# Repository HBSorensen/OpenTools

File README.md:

# OpenTools
Collection of  Tools (Both hardware and software) for various software and hardware development

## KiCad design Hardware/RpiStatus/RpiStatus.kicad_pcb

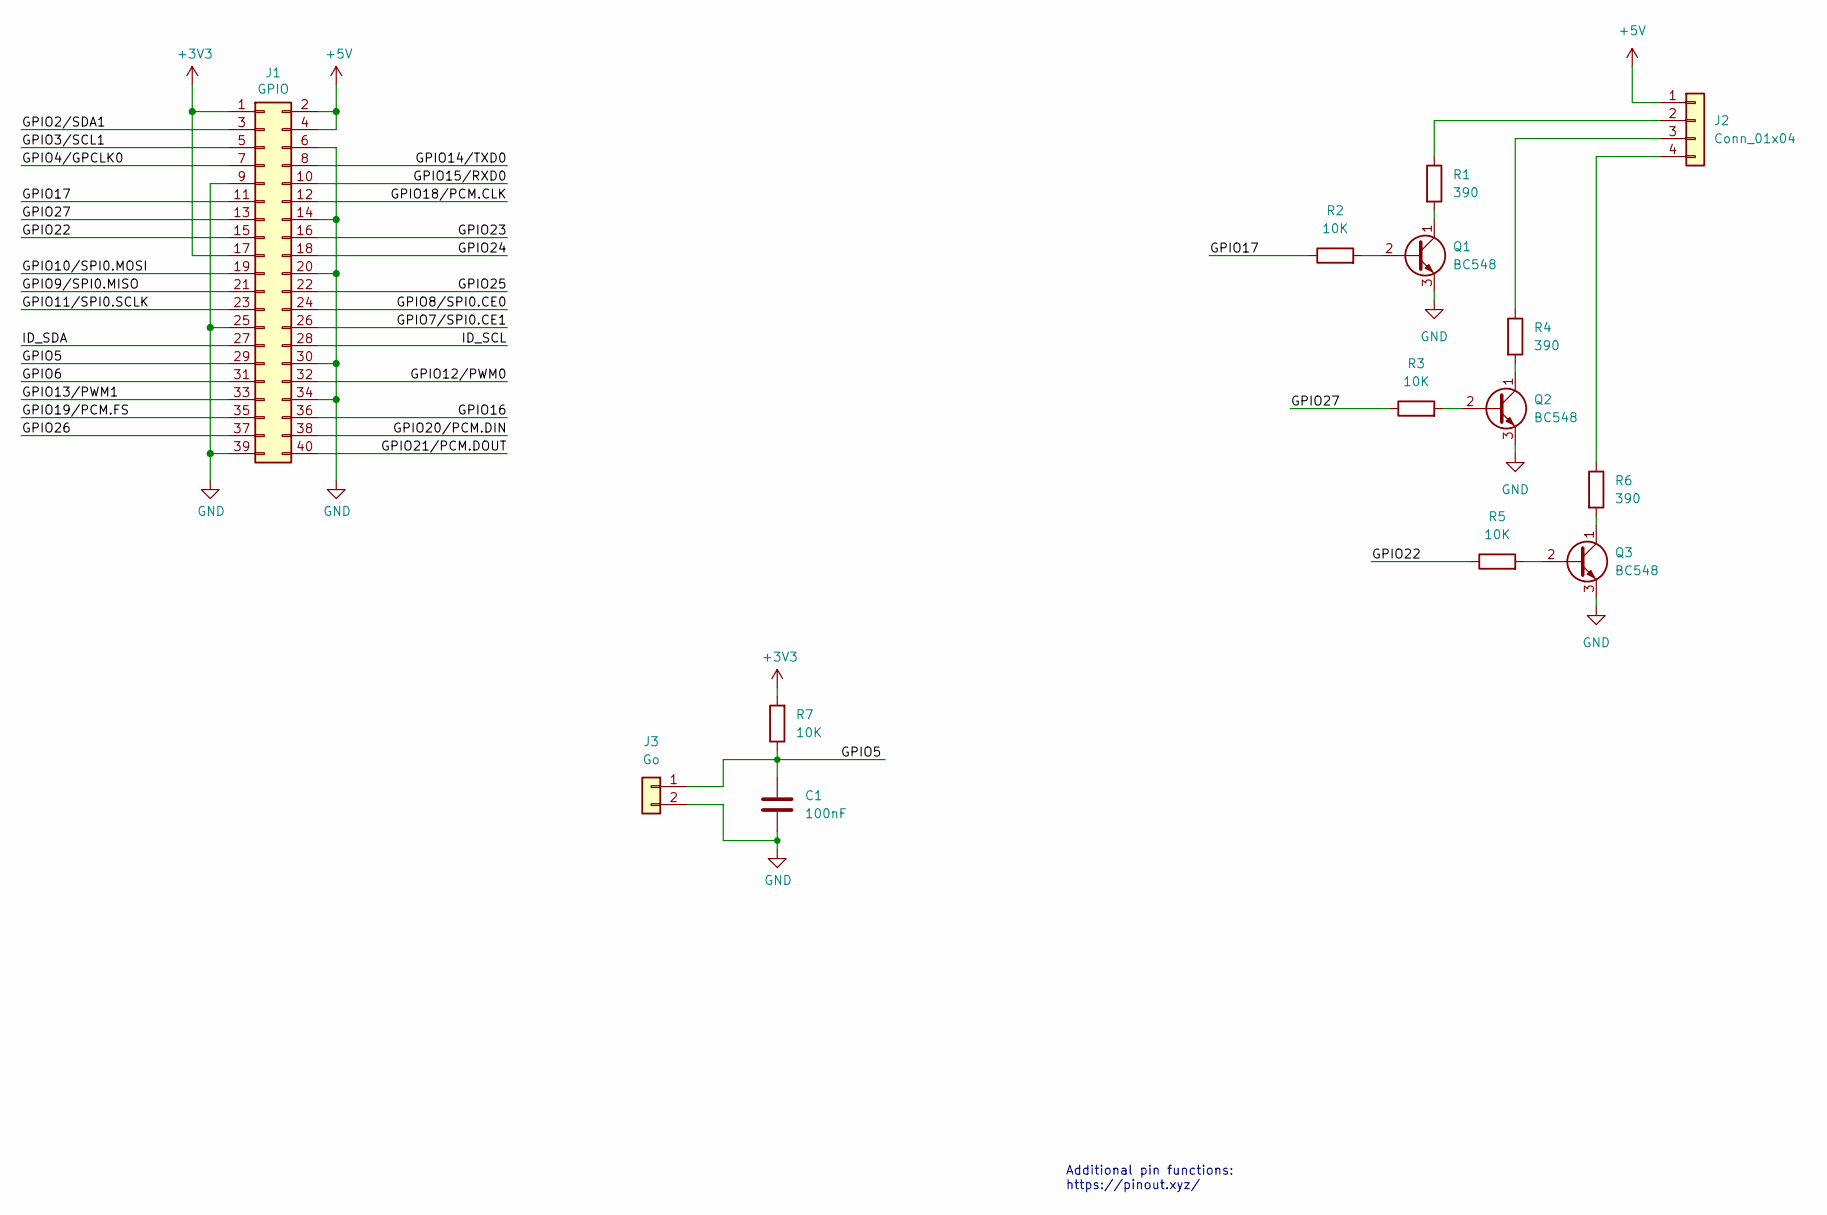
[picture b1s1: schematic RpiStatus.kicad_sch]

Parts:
C1: 100nF; C_Rect_L10.0mm_W5.0mm_P5.00mm_P7.50mm
J1: GPIO; PinSocket_2x20_P2.54mm_Vertical
J2: Conn_01x04; PinSocket_1x04_P2.54mm_Vertical
J3: Go; SW_PUSH_6mm_H7.3mm
Q1, Q2, Q3: BC548; TO-92L_Wide
R1, R4, R6: 390; R_Axial_DIN0204_L3.6mm_D1.6mm_P7.62mm_Horizontal
R2, R3, R5, R7: 10K; R_Axial_DIN0204_L3.6mm_D1.6mm_P7.62mm_Horizontal

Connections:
+3V3: J1.1, J1.17, R7.2
+5V: J1.2, J1.4, J2.1
/GPIO2/SDA1: J1.3
/GPIO3/SCL1: J1.5
/GPIO4/GPCLK0: J1.7
/GPIO5: C1.1, J1.29, J3.1, R7.1
/GPIO6: J1.31
/GPIO7/SPI0.CE1: J1.26
/GPIO8/SPI0.CE0: J1.24
/GPIO9/SPI0.MISO: J1.21
/GPIO10/SPI0.MOSI: J1.19
/GPIO11/SPI0.SCLK: J1.23
/GPIO12/PWM0: J1.32
/GPIO13/PWM1: J1.33
/GPIO14/TXD0: J1.8
/GPIO15/RXD0: J1.10
/GPIO16: J1.36
/GPIO17: J1.11, R2.1
/GPIO18/PCM.CLK: J1.12
/GPIO19/PCM.FS: J1.35
/GPIO20/PCM.DIN: J1.38
/GPIO21/PCM.DOUT: J1.40
/GPIO22: J1.15, R5.1
/GPIO23: J1.16
/GPIO24: J1.18
/GPIO25: J1.22
/GPIO26: J1.37
/GPIO27: J1.13, R3.1
/ID_SCL: J1.28
/ID_SDA: J1.27
GND: C1.2, J1.6, J1.9, J1.14, J1.20, J1.25, J1.30, J1.34, J1.39, J3.2, Q1.3 (E), Q2.3 (E), Q3.3 (E)
unnamed: J2.2, R1.1
unnamed: J2.3, R4.1
unnamed: J2.4, R6.1
unnamed: Q1.2 (B), R2.2
unnamed: Q1.1 (C), R1.2
unnamed: Q2.2 (B), R3.2
unnamed: Q2.1 (C), R4.2
unnamed: Q3.2 (B), R5.2
unnamed: Q3.1 (C), R6.2

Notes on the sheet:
Additional pin functions: https://pinout.xyz/

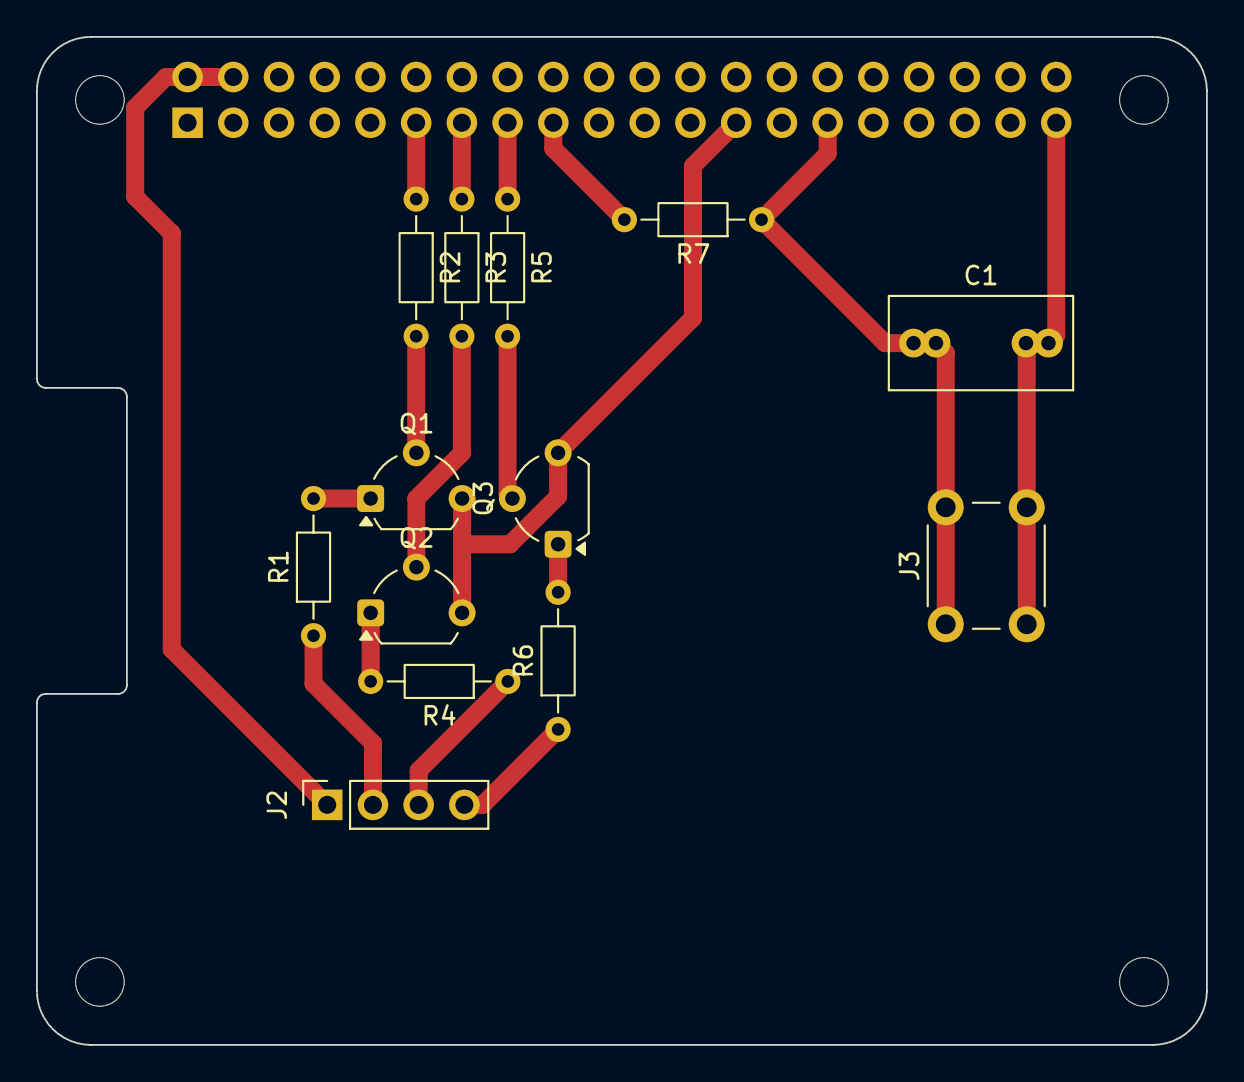
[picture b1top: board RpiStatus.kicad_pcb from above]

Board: 2 copper layers, 65.0 x 56.0 mm, 18 parts (1 on the bottom side), 16 nets.

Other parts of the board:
MH1, MH2, MH3, MH4: MountingHole_2.7mm_M2.5

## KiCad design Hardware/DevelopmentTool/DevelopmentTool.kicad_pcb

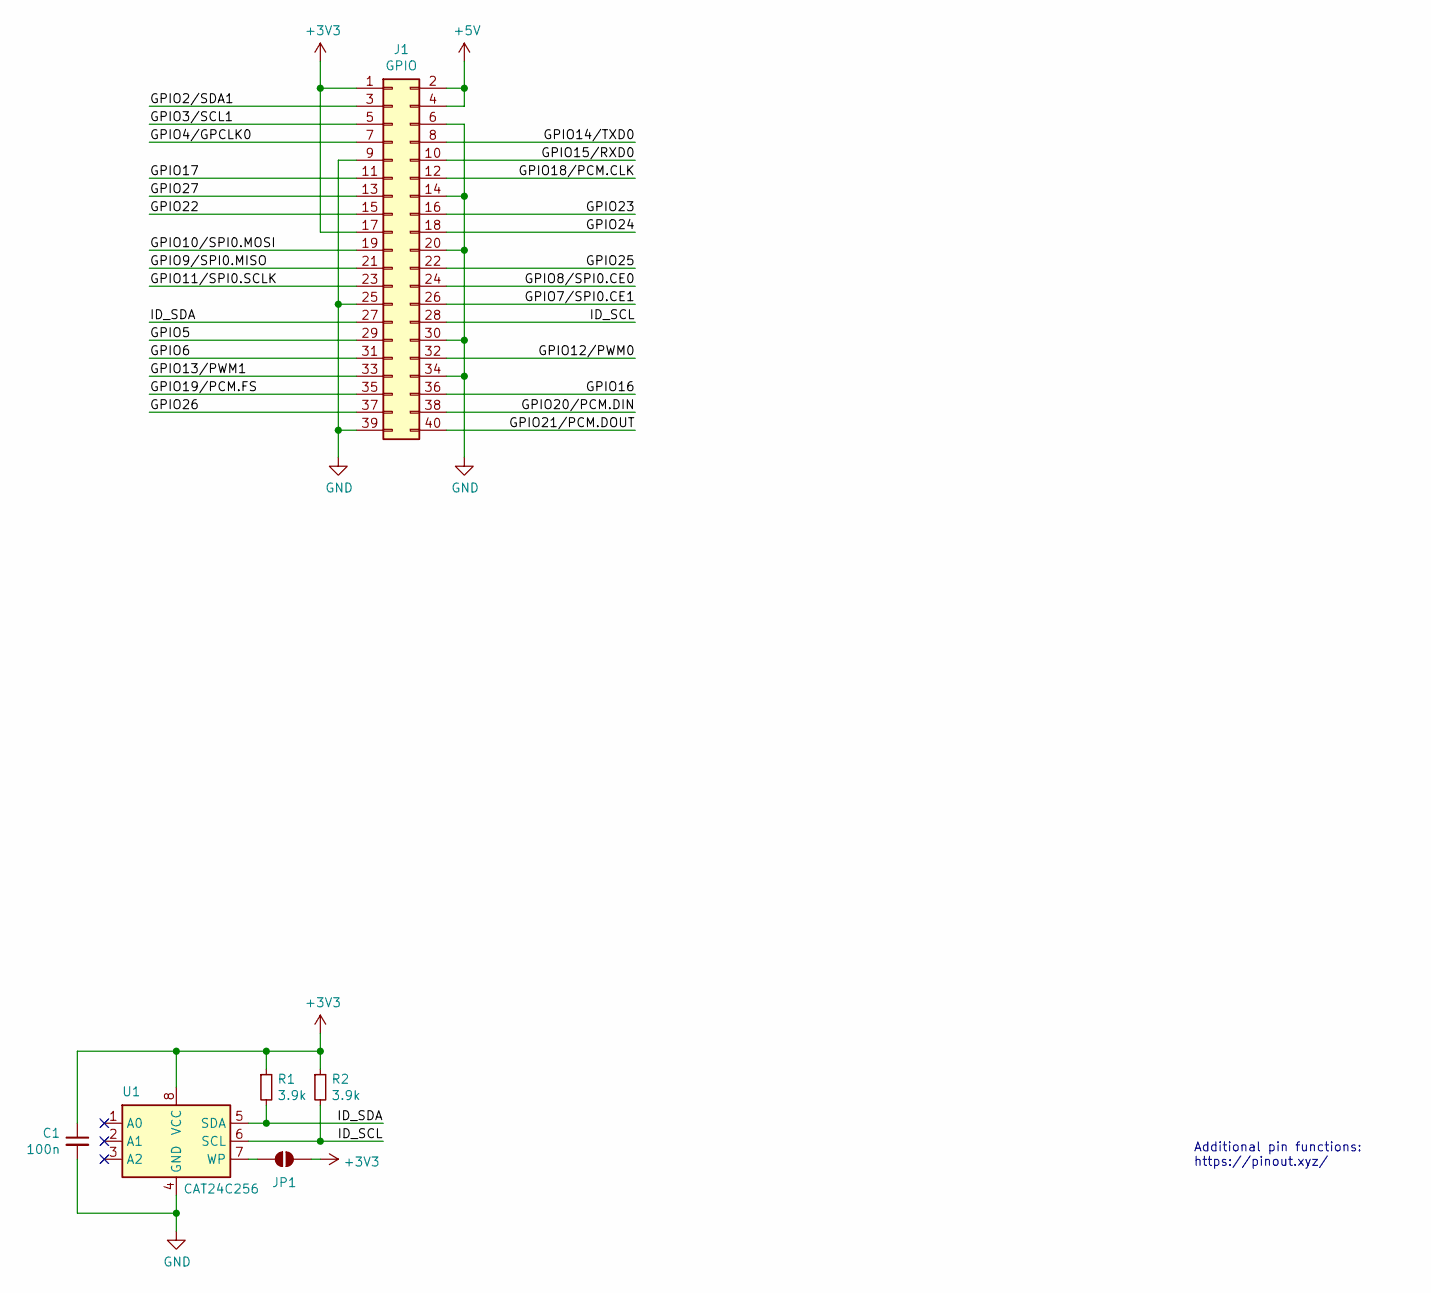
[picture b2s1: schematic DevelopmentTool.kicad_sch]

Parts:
C1: 100n; C_0603_1608Metric
J1: GPIO; PinSocket_2x20_P2.54mm_Vertical
JP1: ID_WP; SolderJumper-2_P1.3mm_Open_RoundedPad1.0x1.5mm
R1, R2: 3.9k; R_0603_1608Metric
U1: CAT24C256; SO-8_3.9x4.9mm_P1.27mm

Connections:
+3V3: C1.1, J1.1, J1.17, JP1.2 (B), R1.1, R2.1, U1.8 (VCC)
+5V: J1.2, J1.4
/GPIO2/SDA1: J1.3
/GPIO3/SCL1: J1.5
/GPIO4/GPCLK0: J1.7
/GPIO5: J1.29
/GPIO6: J1.31
/GPIO7/SPI0.CE1: J1.26
/GPIO8/SPI0.CE0: J1.24
/GPIO9/SPI0.MISO: J1.21
/GPIO10/SPI0.MOSI: J1.19
/GPIO11/SPI0.SCLK: J1.23
/GPIO12/PWM0: J1.32
/GPIO13/PWM1: J1.33
/GPIO14/TXD0: J1.8
/GPIO15/RXD0: J1.10
/GPIO16: J1.36
/GPIO17: J1.11
/GPIO18/PCM.CLK: J1.12
/GPIO19/PCM.FS: J1.35
/GPIO20/PCM.DIN: J1.38
/GPIO21/PCM.DOUT: J1.40
/GPIO22: J1.15
/GPIO23: J1.16
/GPIO24: J1.18
/GPIO25: J1.22
/GPIO26: J1.37
/GPIO27: J1.13
/ID_SCL: J1.28, R2.2, U1.6 (SCL)
/ID_SDA: J1.27, R1.2, U1.5 (SDA)
GND: C1.2, J1.6, J1.9, J1.14, J1.20, J1.25, J1.30, J1.34, J1.39, U1.4 (GND)
unnamed: JP1.1 (A), U1.7 (WP)

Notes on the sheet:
Additional pin functions: https://pinout.xyz/

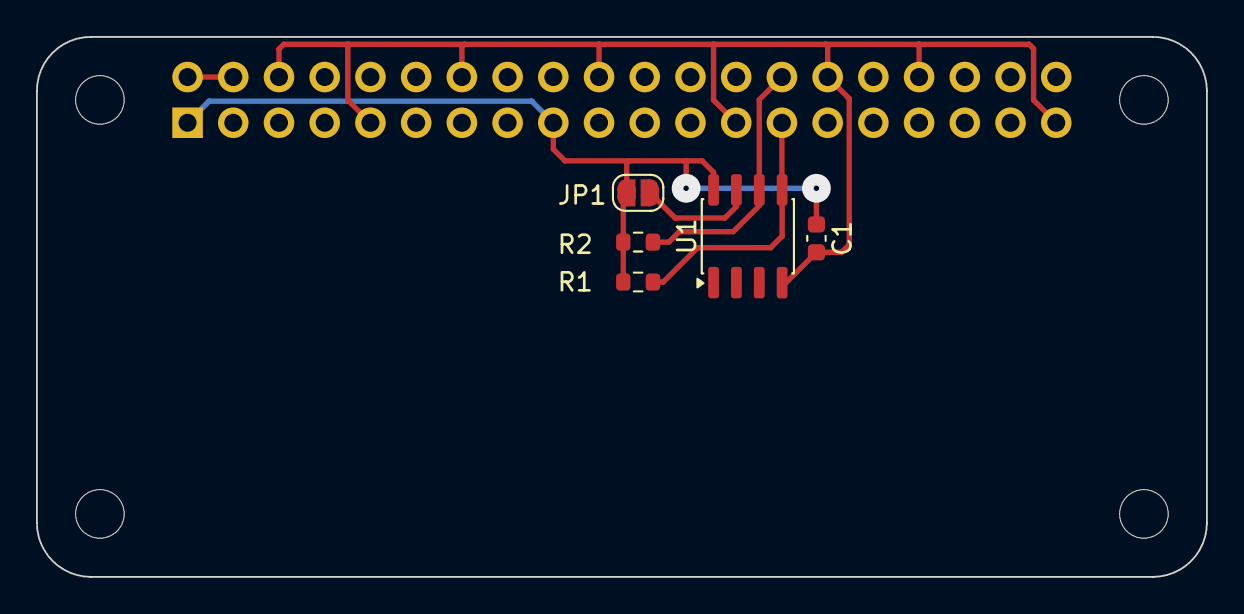
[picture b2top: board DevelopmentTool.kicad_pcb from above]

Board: 2 copper layers, 65.0 x 30.0 mm, 10 parts (1 on the bottom side), 6 nets.

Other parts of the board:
MH1, MH2, MH3, MH4: MountingHole_2.7mm_M2.5
